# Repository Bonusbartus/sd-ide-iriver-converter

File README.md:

# 44 pin 2.5" IDE to 44pin 1,8" IDE converter for Iriver H1XX/H3XX project
This PCB, designed using KiCad, was design to be used with an SD-Card to IDE converter.
These converters come with 44pin IDE connectors used on 2,5" Harddisks.
These old MP3 players (and others) used 1,8" Harddisk, which have a smaller pin spacing (1.27mm instead of 2,0mm)
In order to connect an SD-Card to IDE converter to the Iriver H120 44pin HDD connector, within the limited room of the player,
I though it was easiest to use this PCB design as an edge connector.
On One side the PCB can be soldered between the 2 rows of pins of the IDE converter, on the other side a 1,27mm spaced 44x2 connector can be soldered,
with its pins on both sides of the PCB. In order to fit, the PCB has been set up to be 0.8mm thick

# SW Version
* KiCad 7.0
## TODO's
solder pads for both footprints might be made a little longer, now when putting it together, the connector pins cover the entire solder pads (in width and length)
## BOM
Besides the SD-Card to IDE converter [Aliexpress](https://nl.aliexpress.com/item/4001146603163.html), only one component is needed:
* Double row 44(50) pin 1.27mm female connector [Aliexpress](https://nl.aliexpress.com/item/4001127977216.html)
## Pictures

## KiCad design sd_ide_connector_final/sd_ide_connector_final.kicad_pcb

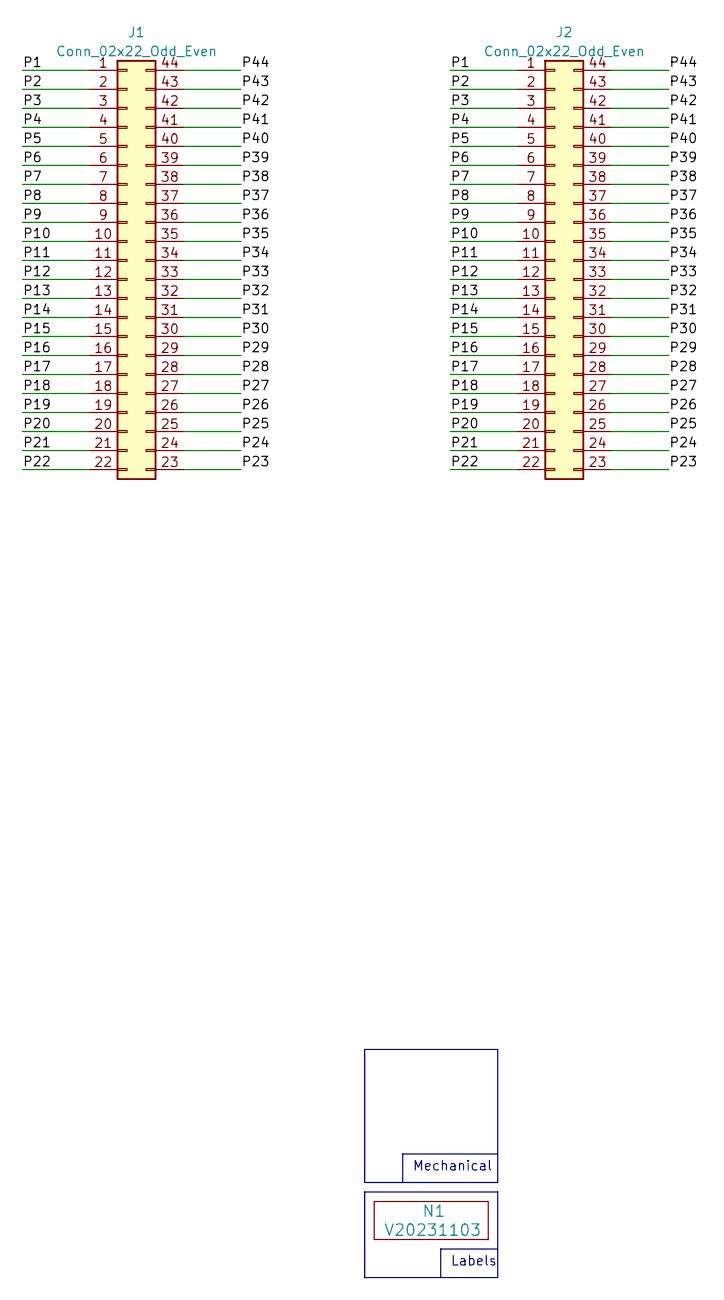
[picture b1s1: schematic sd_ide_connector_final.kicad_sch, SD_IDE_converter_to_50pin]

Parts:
J1: Conn_02x22_Odd_Even; PCB_Edge_header_2x22_P2.00mm_receive_male
J2: Conn_02x22_Odd_Even; PCB_Edge_header_2x22_P1.27mm_receive_male
N1: V20231103; Label_Generic

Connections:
/P1: J1.1, J2.1
/P2: J1.2, J2.2
/P3: J1.3, J2.3
/P4: J1.4, J2.4
/P5: J1.5, J2.5
/P6: J1.6, J2.6
/P7: J1.7, J2.7
/P8: J1.8, J2.8
/P9: J1.9, J2.9
/P10: J1.10, J2.10
/P11: J1.11, J2.11
/P12: J1.12, J2.12
/P13: J1.13, J2.13
/P14: J1.14, J2.14
/P15: J1.15, J2.15
/P16: J1.16, J2.16
/P17: J1.17, J2.17
/P18: J1.18, J2.18
/P19: J1.19, J2.19
/P20: J1.20, J2.20
/P21: J1.21, J2.21
/P22: J1.22, J2.22
/P23: J1.23, J2.23
/P24: J1.24, J2.24
/P25: J1.25, J2.25
/P26: J1.26, J2.26
/P27: J1.27, J2.27
/P28: J1.28, J2.28
/P29: J1.29, J2.29
/P30: J1.30, J2.30
/P31: J1.31, J2.31
/P32: J1.32, J2.32
/P33: J1.33, J2.33
/P34: J1.34, J2.34
/P35: J1.35, J2.35
/P36: J1.36, J2.36
/P37: J1.37, J2.37
/P38: J1.38, J2.38
/P39: J1.39, J2.39
/P40: J1.40, J2.40
/P41: J1.41, J2.41
/P42: J1.42, J2.42
/P43: J1.43, J2.43
/P44: J1.44, J2.44

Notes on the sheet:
Labels
Mechanical

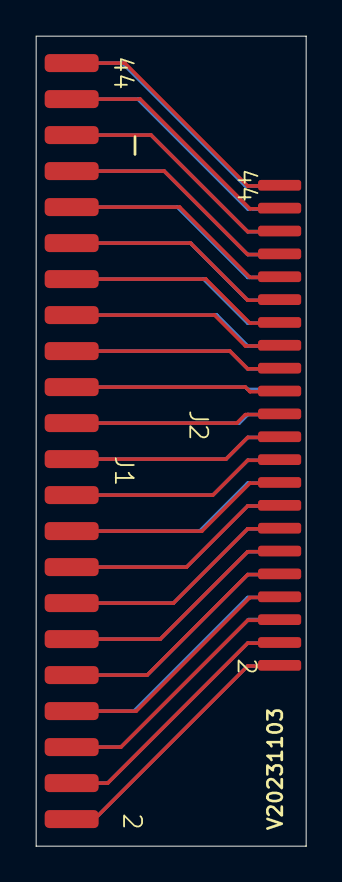
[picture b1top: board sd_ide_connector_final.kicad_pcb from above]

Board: 2 copper layers, 15.0 x 45.0 mm, 3 parts (0 on the bottom side), 44 nets.

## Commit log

2023-11-22 initial final commit
